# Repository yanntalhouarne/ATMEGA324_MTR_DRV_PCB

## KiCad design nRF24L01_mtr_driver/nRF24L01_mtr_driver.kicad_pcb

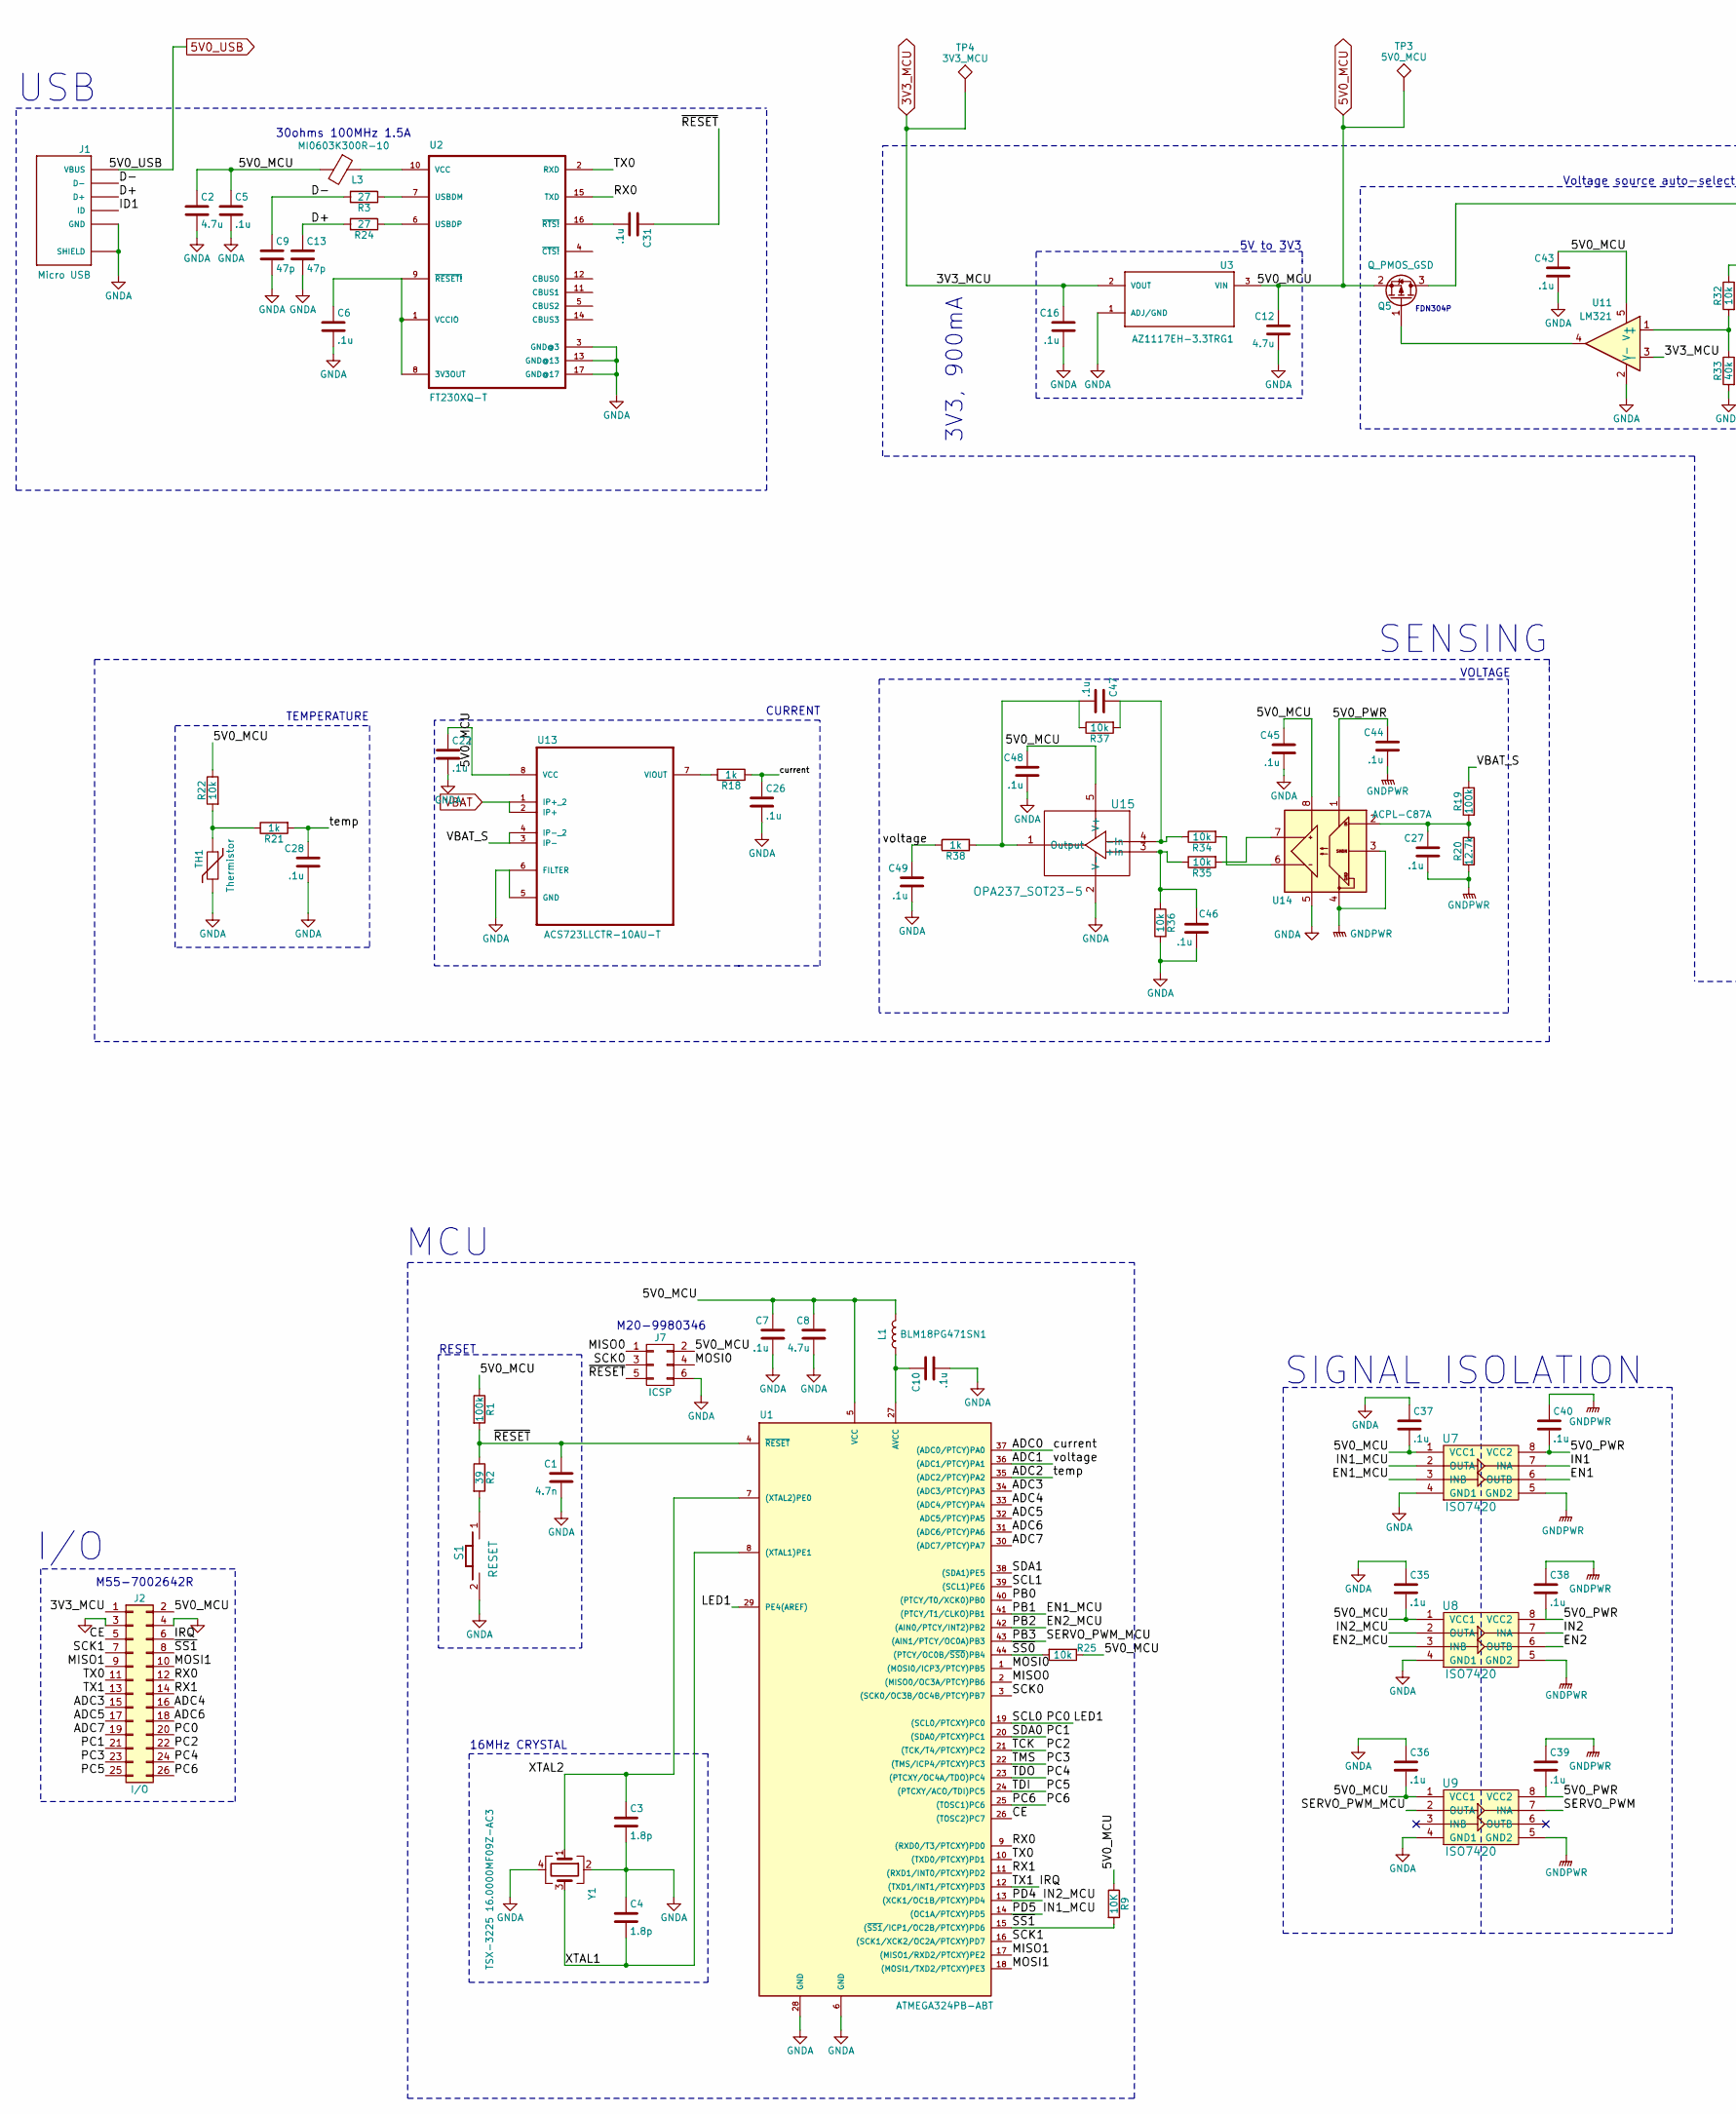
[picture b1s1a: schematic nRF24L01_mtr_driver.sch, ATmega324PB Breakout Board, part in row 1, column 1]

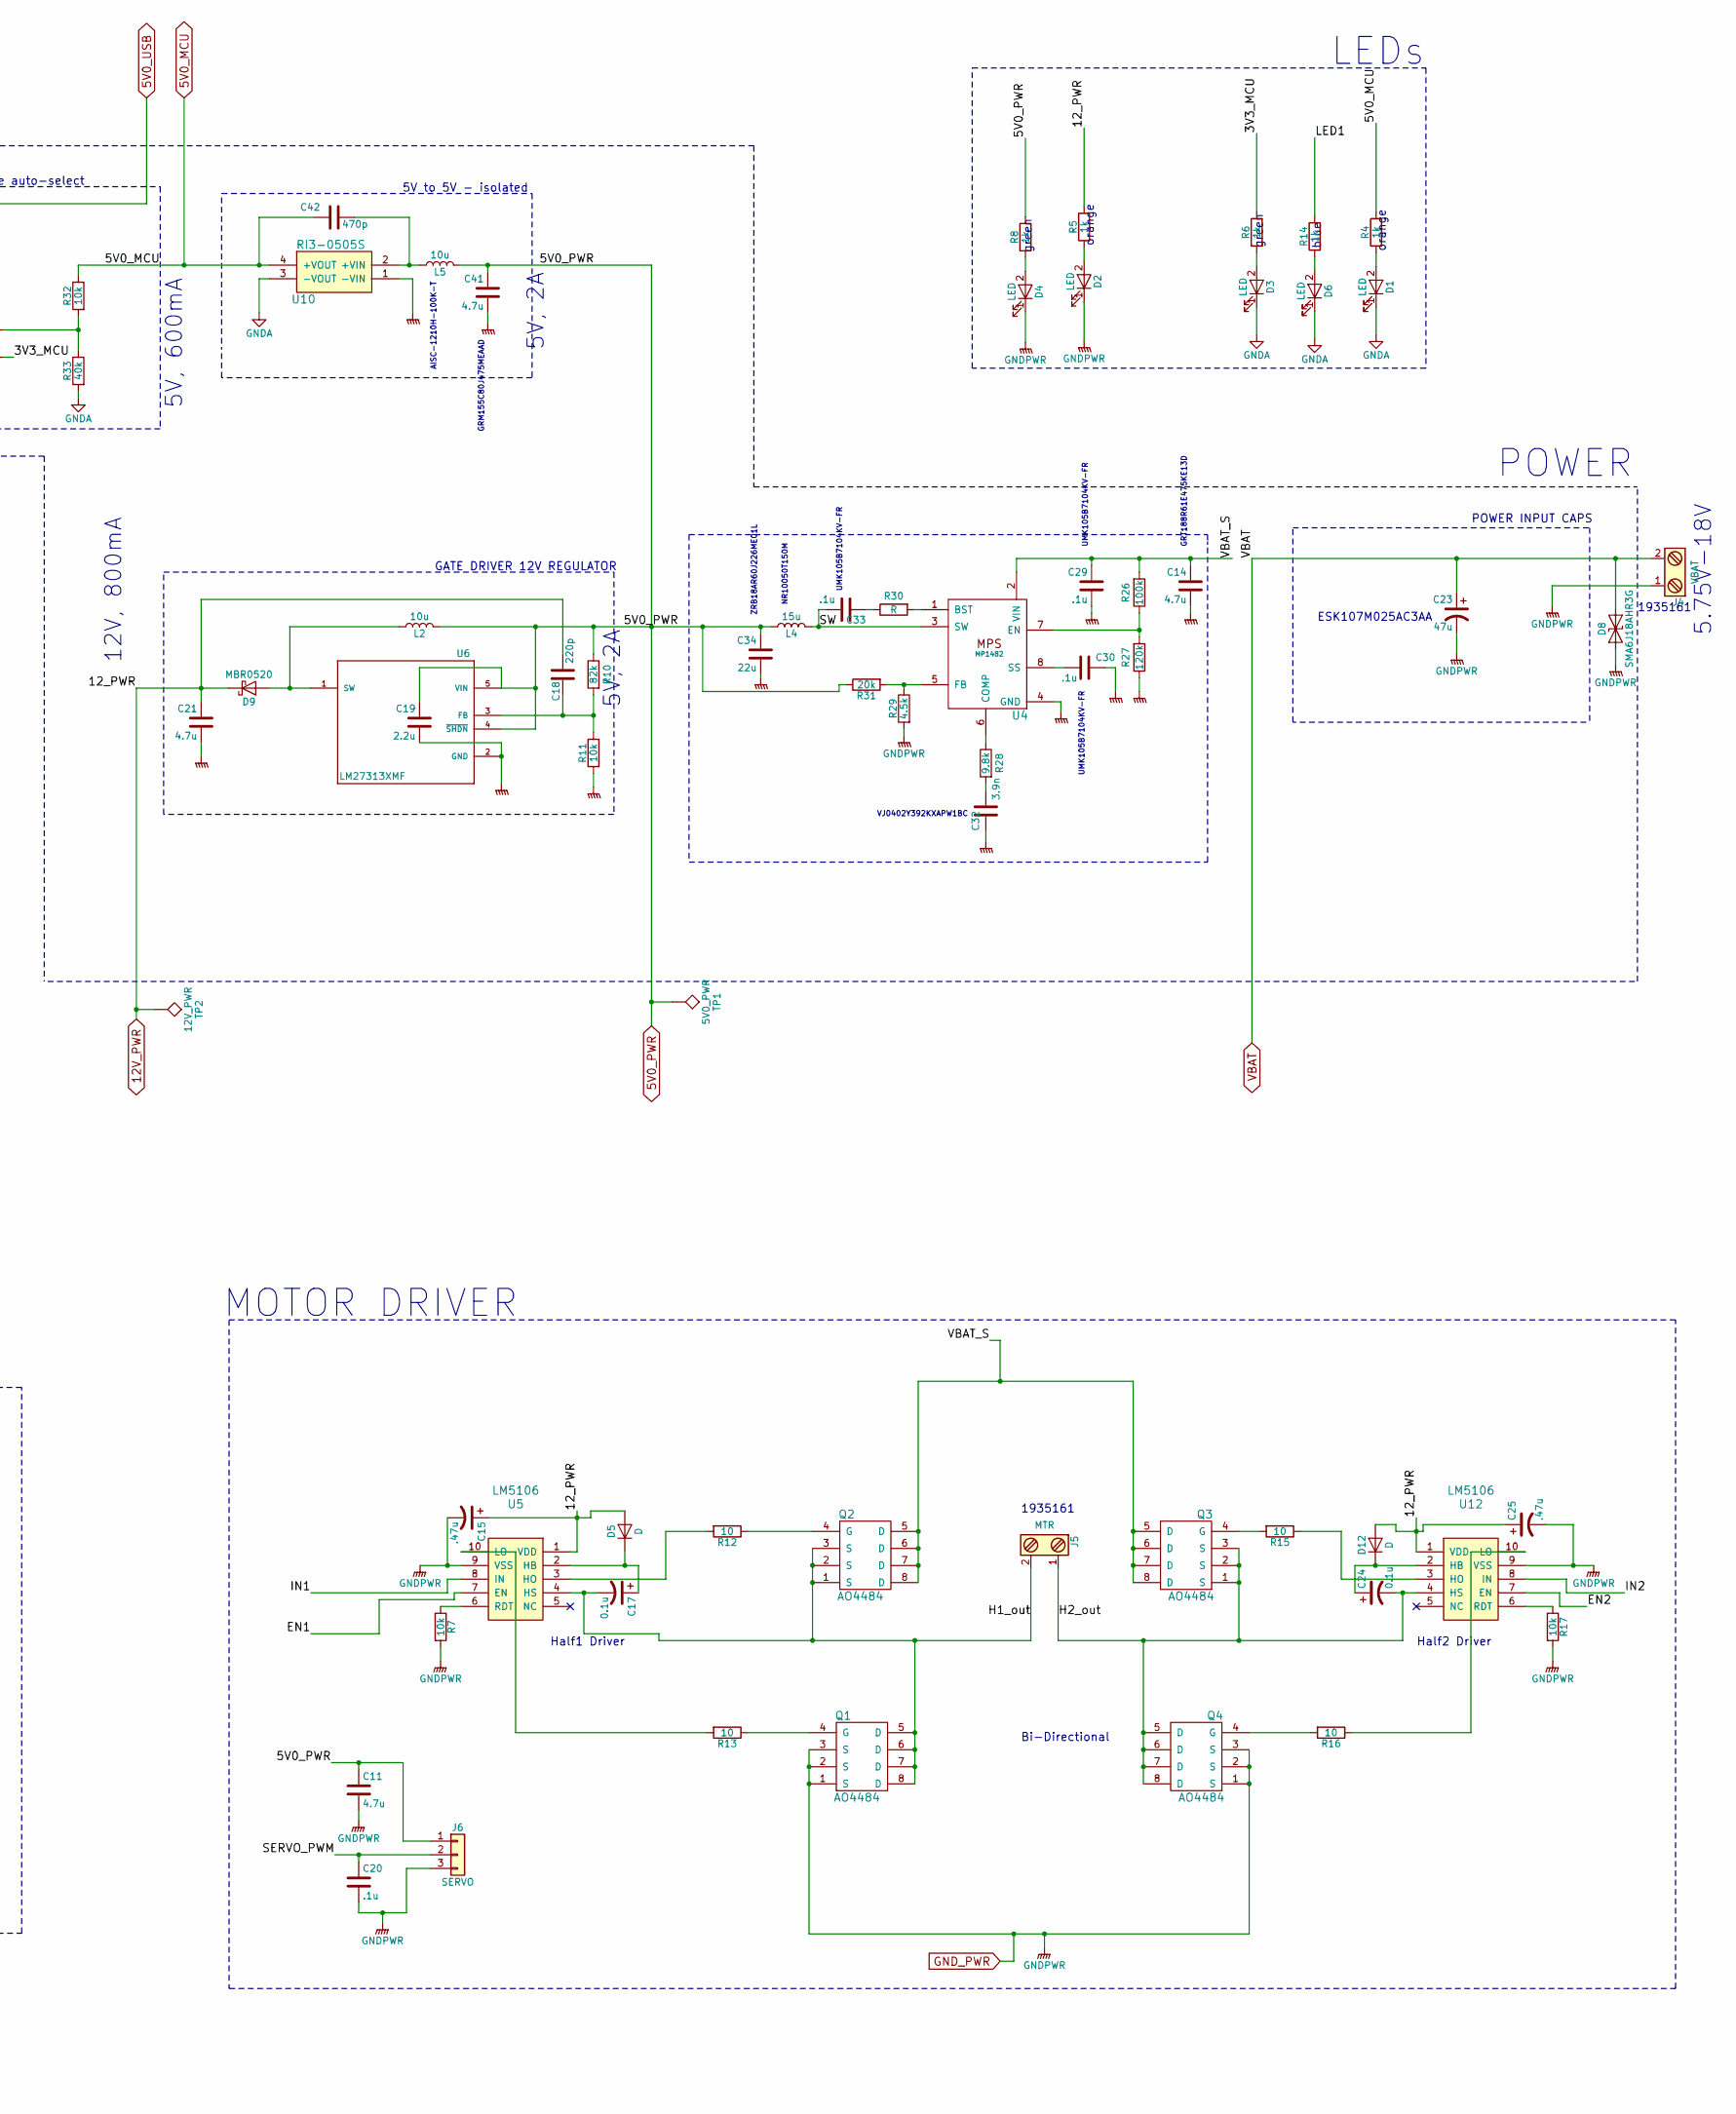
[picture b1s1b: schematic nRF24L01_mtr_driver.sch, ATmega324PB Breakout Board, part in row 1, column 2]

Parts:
C1: 4.7n; C_0402
C2, C11, C14: 4.7u; C_0603
C3, C4: 1.8p; C_0402
C5, C6, C7, C10, C16, C20, C22, C26, C27, C28, C30, C31, C33, C35, C36, C37, C38, C39, C40, C43, C44, C45, C46, C47, C48, C49: .1u; C_0402
C8, C12, C41: 4.7u; C_0402
C9, C13: 47p; C_0402
C15, C25: .47u; C_0603
C17, C24: 0.1u; C_0603
C18: 220p; C_0402
C19: 2.2u; C_0603
C21: 4.7u; C_0805
C23: 47u; D5_P2_cap
C29: .1u; C_0805
C32: 3.9n; C_0402
C34: 22u; C_0805
C42: 470p; C_0402
D1, D2, D3, D4, D6: LED; LED_0603
D5, D12: D; D_0603
D8: SMA6J18AHR3G; DO-214AC
D9: MBR0520; D_SOD-123
J1: Micro USB; USB_10118192-0001LF
J2: I/O; M55-60zzz42R
J4: VBAT; PHOENIX_1935161
J5: MTR; PHOENIX_1935161
J6: SERVO; Pin_Header_Straight_1x03_Pitch2.54mm
J7: ICSP; Pin_Header_Straight_2x03_Pitch2.54mm
L1: BLM18PG471SN1; L_0603
L2: 10u; C_0805
L3: MI0603K300R-10; L_0603
L4: 15u; SMD_1005
L5: 10u; L_1210
Q1, Q2, Q3, Q4: AO4484; SOIC-8-N
Q5: Q_PMOS_GSD; SOT-23
R1, R19, R26: 100k; R_0402
R2: 39; R_0402
R3, R24: 27; R_0402
R4, R5, R6, R8, R14, R18, R21, R38: 1k; R_0402
R7, R11, R17, R22, R25, R32, R34, R35, R36, R37: 10k; R_0402
R9: 10K; R_0402
R10: 82k; R_0402
R12, R13, R15, R16: 10; R_0402
R20: 12.7k; R_0402
R27: 120k; R_0402
R28: 9.8k; R_0402
R29: 4.5k; R_0402
R30: R; R_0402
R31: 20k; R_0402
R33: 40k; R_0402
S1: RESET; SW_SPST_KMR2
TH1: Thermistor; R_0603
TP1: 5V0_PWR; Measurement_Point_Square-SMD-Pad_Small
TP2: 12V_PWR; Measurement_Point_Square-SMD-Pad_Small
TP3: 5V0_MCU; Measurement_Point_Square-SMD-Pad_Small
TP4: 3V3_MCU; Measurement_Point_Square-SMD-Pad_Small
U1: ATMEGA324PB-ABT; QFP80P1200X1200X120-44N
U2: FT230XQ-T; QFN16
U3: AZ1117EH-3.3TRG1; SOT229P700X180-4N
U4: MP1482; ISO_7420
U5, U12: LM5106; VSSOP-8_2.4x2.1mm_Pitch0.5mm
U6: LM27313XMF; SOT95P285X120-5N
U7, U8, U9: ISO7420; ISO_7420
U10: RI3-0505S; ROE_0505S
U11: LM321; SOT-23-5
U13: ACS723LLCTR-10AU-T; SOIC-8-N
U14: ACPL-C87A; SSO-8_6.8x5.9mm_Pitch1.27mm_Clearance8mm
U15: OPA237_SOT23-5; SOT-23-5
Y1: TSX-3225 16.0000MF09Z-AC3

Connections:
3V3_MCU: C16.1, J2.1, R6.1, TP4.1, U3.2 (VOUT), U11.3 (-)
5V0_MCU: C2.1, C5.1, C7.1, C8.1, C12.1, C22.1, C35.2, C36.2, C37.2, C42.1, C43.1, C45.1, C48.1, J2.2, J7.2, L1.2, L3.2, Q5.2 (S), R1.1, R4.1, R9.1, R22.1, R25.1, R32.1, TP3.1, U1.5 (VCC), U3.3 (VIN), U7.1 (VCC1), U8.1 (VCC1), U9.1 (VCC1), U10.4 (+VOUT), U11.5 (V+), U13.8 (VCC), U14.8 (VDD2), U15.5 (V+)
5V0_PWR: C11.1, C19.1, C34.1, C38.2, C39.2, C40.2, C41.1, C44.1, J6.1, L2.1, L4.2, L5.1, R8.1, R10.1, R31.1, TP1.1, U6.4 (~SHDN), U6.5 (VIN), U7.8 (VCC2), U8.8 (VCC2), U9.8 (VCC2), U14.1 (VDD1)
5V0_USB: J1.1 (VBUS), Q5.3 (D)
12V_PWR: C15.1, C18.1, C21.1, C25.1, D5.2 (A), D9.1 (K), D12.2 (A), R5.1, TP2.1, U5.1 (VDD), U12.1 (VDD)
/ADC0: C26.1, R18.1, U1.37 ((ADC0/PTCY)PA0)
/ADC1: C49.1, R38.1, U1.36 ((ADC1/PTCY)PA1)
/ADC2: C28.1, R21.2, U1.35 ((ADC2/PTCY)PA2)
/ADC3: J2.15, U1.34 ((ADC3/PTCY)PA3)
/ADC4: J2.16, U1.33 ((ADC4/PTCY)PA4)
/ADC5: J2.17, U1.32 (ADC5/PTCY)PA5)
/ADC6: J2.18, U1.31 ((ADC6/PTCY)PA6)
/ADC7: J2.19, U1.30 ((ADC7/PTCY)PA7)
/CE: J2.5, U1.26 ((TOSC2)PC7)
/D+: C13.1, J1.3 (D+), R24.2
/D-: C9.1, J1.2 (D-), R3.2
/EN1: U5.7 (EN), U7.6 (OUTB)
/EN1_MCU: U1.41 ((PTCY/T1/CLKO)PB1), U7.3 (INB)
/EN2: U8.6 (OUTB), U12.7 (EN)
/EN2_MCU: U1.42 ((AIN0/PTCY/INT2)PB2), U8.3 (INB)
/H1_out: C17.2, J5.2, Q1.5 (D), Q1.6 (D), Q1.7 (D), Q1.8 (D), Q2.1 (S), Q2.2 (S), Q2.3 (S), U5.4 (HS)
/H2_out: C24.2, J5.1, Q3.1 (S), Q3.2 (S), Q3.3 (S), Q4.5 (D), Q4.6 (D), Q4.7 (D), Q4.8 (D), U12.4 (HS)
/ID1: J1.4 (ID)
/IN1: U5.8 (IN), U7.7 (INA)
/IN1_MCU: U1.14 ((OC1A/PTCXY)PD5), U7.2 (OUTA)
/IN2: U8.7 (INA), U12.8 (IN)
/IN2_MCU: U1.13 ((XCK1/OC1B/PTCXY)PD4), U8.2 (OUTA)
/IRQ: J2.6, J2.13, U1.12 ((TXD1/INT1/PTCXY)PD3)
/LED1: J2.20, R14.1, U1.19 ((SCL0/PTCXY)PC0), U1.29 (PE4(AREF))
/MISO0: J7.1, U1.2 ((MISO0/OC3A/PTCY)PB6)
/MISO1: J2.9, U1.17 ((MISO1/RXD2/PTCXY)PE2)
/MOSI0: J7.4, U1.1 ((MOSI0/ICP3/PTCY)PB5)
/MOSI1: J2.10, U1.18 ((MOSI1/TXD2/PTCXY)PE3)
/PB0: U1.40 ((PTCY/T0/XCK0)PB0)
/PB3: U1.43 ((AIN1/PTCY/OC0A)PB3), U9.2 (OUTA)
/PC1: J2.21, U1.20 ((SDA0/PTCXY)PC1)
/PC2: J2.22, U1.21 ((TCK/T4/PTCXY)PC2)
/PC3: J2.23, U1.22 ((TMS/ICP4/PTCXY)PC3)
/PC4: J2.24, U1.23 ((PTCXY/OC4A/TDO)PC4)
/PC5: J2.25, U1.24 ((PTCXY/ACO/TDI)PC5)
/PC6: J2.26, U1.25 ((TOSC1)PC6)
/RX0: J2.12, U1.9 ((RXD0/T3/PTCXY)PD0), U2.15 (TXD)
/RX1: J2.14, U1.11 ((RXD1/INT0/PTCXY)PD2)
/SCK0: J7.3, U1.3 ((SCK0/OC3B/OC4B/PTCY)PB7)
/SCK1: J2.7, U1.16 ((SCK1/XCK2/OC2A/PTCXY)PD7)
/SCL1: U1.39 ((SCL1)PE6)
/SDA1: U1.38 ((SDA1)PE5)
/SERVO_PWM: C20.1, J6.2, U9.7 (INA)
/SW: C33.1, L4.1, U4.3 (SW)
/TX0: J2.11, U1.10 ((TXD0/PTCXY)PD1), U2.2 (RXD)
/VBAT_S: C14.1, C29.1, Q2.5 (D), Q2.6 (D), Q2.7 (D), Q2.8 (D), Q3.5 (D), Q3.6 (D), Q3.7 (D), Q3.8 (D), R19.1, R26.2, U4.2 (VIN), U13.3 (IP-), U13.4 (IP-_2)
/XTAL1: C4.2, U1.8 ((XTAL1)PE1), Y1.3
/XTAL2: C3.1, U1.7 ((XTAL2)PE0), Y1.1
/~RESET: C1.1, C31.1, J7.5, R1.2, R2.1, U1.4 (~RESET)
/~SS0~: R25.2, U1.44 ((PTCY/OC0B/~SS0~)PB4)
/~SS1~: J2.8, R9.2, U1.15 ((~SS1~/ICP1/OC2B/PTCXY)PD6)
GNDA: C1.2, C2.2, C3.2, C4.1, C5.2, C6.2, C7.2, C8.2, C9.2, C10.2, C12.2, C13.2, C16.2, C22.2, C26.2, C28.2, C35.1, C36.1, C37.1, C43.2, C45.2, C46.2, C48.2, C49.2, D1.1 (K), D3.1 (K), D6.1 (K), J1.5 (GND), J1.6 (SHIELD), J1.7 (SHIELD), J1.8 (SHIELD), J1.9 (SHIELD), J2.3, J2.4, J7.6, R33.2, R36.1, S1.2, TH1.2, U1.6 (GND), U1.28 (GND), U2.3 (GND@3), U2.13 (GND@13), U2.17 (GND@17), U3.1 (ADJ/GND), U7.4 (GND1), U8.4 (GND1), U9.4 (GND1), U10.3 (-VOUT), U11.2 (V-), U13.5 (GND), U13.6 (FILTER), U14.5 (GND2), U15.2 (V-), Y1.2, Y1.4
GND_PWR: C11.2, C14.2, C15.2, C19.2, C20.2, C21.2, C23.2, C25.2, C27.2, C29.2, C30.1, C32.2, C34.2, C38.1, C39.1, C40.1, C41.2, C44.2, D2.1 (K), D4.1 (K), D8.2 (A2), J4.1, J6.3, Q1.1 (S), Q1.2 (S), Q1.3 (S), Q4.1 (S), Q4.2 (S), Q4.3 (S), R7.2, R11.2, R17.2, R20.2, R27.1, R29.2, U4.4 (GND), U5.9 (VSS), U6.2 (GND), U7.5 (GND2), U8.5 (GND2), U9.5 (GND2), U10.1 (-VIN), U12.9 (VSS), U14.3 (IN-), U14.4 (GND1)
unnamed: C6.1, U2.1 (VCCIO), U2.8 (3V3OUT), U2.9 (~RESET!~)
unnamed: C10.1, L1.1, U1.27 (AVCC)
unnamed: C17.1, D5.1 (K), U5.2 (HB)
unnamed: C18.2, R10.2, R11.1, U6.3 (FB)
unnamed: C24.1, D12.1 (K), U12.2 (HB)
unnamed: C27.1, R19.2, R20.1, U14.2 (IN)
unnamed: C30.2, U4.8 (SS)
unnamed: C31.2, U2.16 (~RTS!~)
unnamed: C32.1, R28.2
unnamed: C33.2, R30.1
unnamed: C42.2, L5.2, U10.2 (+VIN)
unnamed: C46.1, R35.1, R36.2, U15.3 (+In)
unnamed: C47.1, R34.1, R37.2, U15.4 (-In)
unnamed: C47.2, R37.1, R38.2, U15.1 (Output)
unnamed: D1.2 (A), R4.2
unnamed: D2.2 (A), R5.2
unnamed: D3.2 (A), R6.2
unnamed: D4.2 (A), R8.2
unnamed: D6.2 (A), R14.2
unnamed: D9.2 (A), L2.2, U6.1 (SW)
unnamed: L3.1, U2.10 (VCC)
unnamed: Q1.4 (G), R13.1
unnamed: Q2.4 (G), R12.1
unnamed: Q3.4 (G), R15.2
unnamed: Q4.4 (G), R16.2
unnamed: Q5.1 (G), U11.4
unnamed: R2.2, S1.1
unnamed: R3.1, U2.7 (USBDM)
unnamed: R7.1, U5.6 (RDT)
unnamed: R12.2, U5.3 (HO)
unnamed: R13.2, U5.10 (LO)
unnamed: R15.1, U12.3 (HO)
unnamed: R16.1, U12.10 (LO)
unnamed: R17.1, U12.6 (RDT)
unnamed: R18.2, U13.7 (VIOUT)
unnamed: R21.1, R22.2, TH1.1
unnamed: R24.1, U2.6 (USBDP)
unnamed: R26.1, R27.2, U4.7 (EN)
unnamed: R28.1, U4.6 (COMP)
unnamed: R29.1, R31.2, U4.5 (FB)
unnamed: R30.2, U4.1 (BST)
unnamed: R32.2, R33.1, U11.1 (+)
unnamed: R34.2, U14.6 (OUT-)
unnamed: R35.2, U14.7 (OUT+)
VBAT: C23.1, D8.1 (A1), J4.2, U13.1 (IP+_2), U13.2 (IP+)

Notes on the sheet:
Half1 Driver
Half2 Driver
Bi-Directional
POWER INPUT CAPS
GATE DRIVER 12V REGULATOR
RESET
16MHz CRYSTAL
USB
LEDs
POWER
MCU
MOTOR DRIVER
SENSING
CURRENT
VOLTAGE
TEMPERATURE
1935161
ESK107M025AC3AA
orange
green
blue
5.75V-18V
5V, 2A
12V, 800mA
5V to 5V - isolated
5V to 3V3
SIGNAL ISOLATION
Voltage source auto-select
30ohms 100MHz 1.5A
GRT188R61E475KE13D
UMK105B7104KV-FR
VJ0402Y392KXAPW1BC
NR10050T150M
ZRB18AR60J226ME01L
GRM155C80J475MEAAD
AISC-1210H-100K-T
FDN304P
M55-7002642R
I/O
5V, 600mA

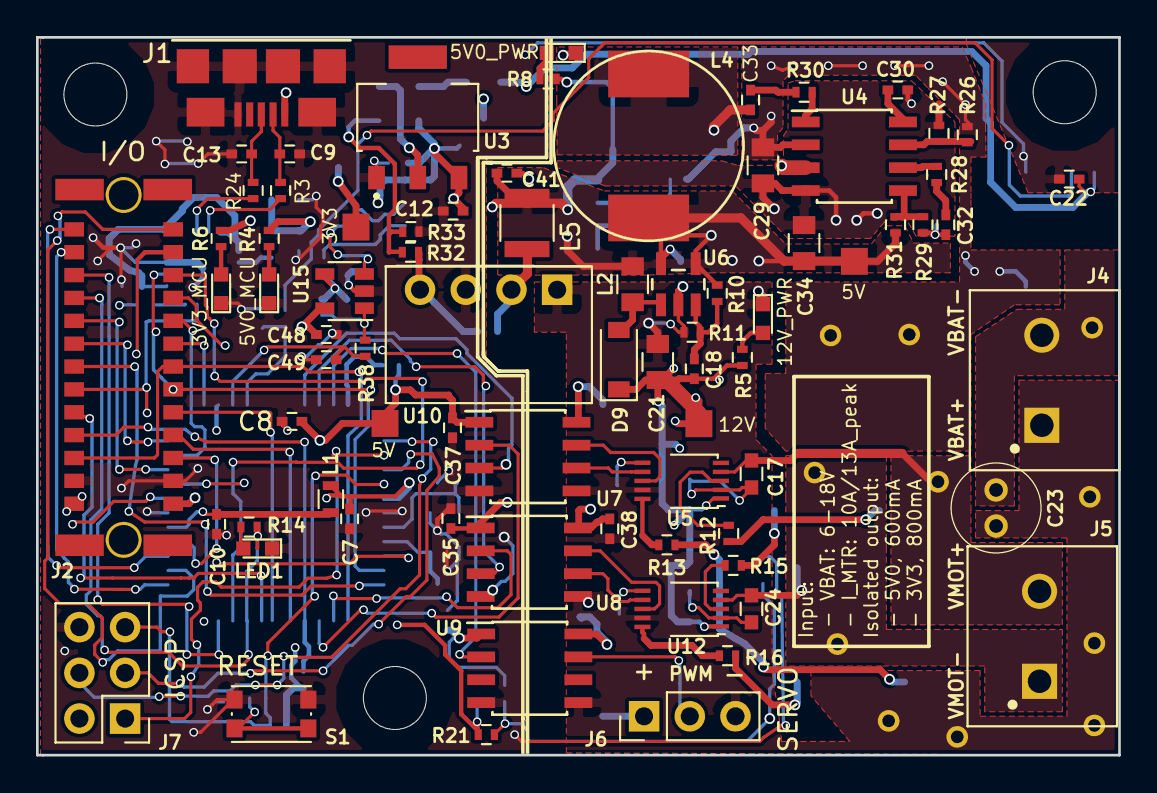
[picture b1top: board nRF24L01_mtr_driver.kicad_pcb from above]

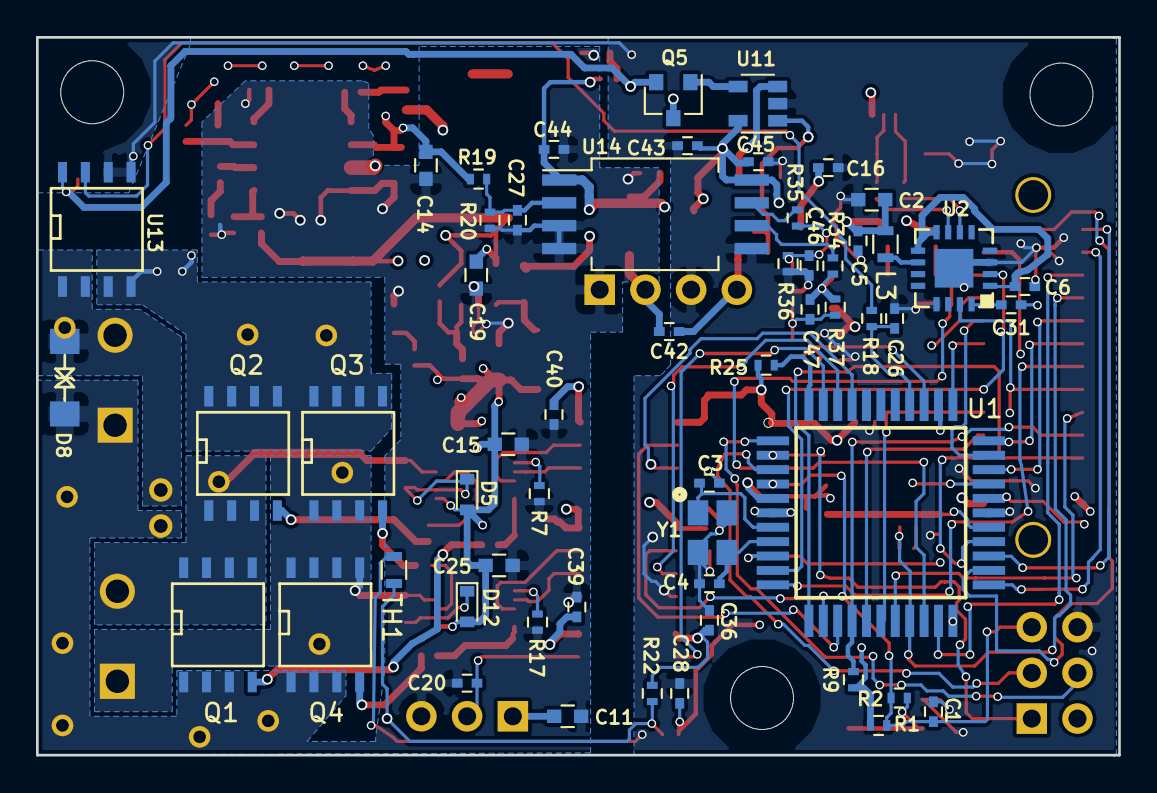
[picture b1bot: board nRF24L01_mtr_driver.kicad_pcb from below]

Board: 4 copper layers, 60.1 x 39.9 mm, 133 parts (56 on the bottom side), 99 nets.

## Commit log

2019-02-23 Added schematic, still need to isolate voltage sense signal
2019-02-24 added voltage sense isolation, needs routing
2019-02-24 Changed the footprint of some 0603 cpacitors to 0402 to save space
2019-02-24 placed major coponents, no routing
2019-02-25 placed most components
2019-02-25 23 components left, stil needs routing
2019-02-28 arranged silkscreen, started rounting (ftdi)
2019-03-16 ready for 2 or 4 layer implementation
2019-03-17 logic side rounting done (4 layer)
2019-03-17 added LED1
2019-03-17 4-layer, most of the routing done (logic + pwr)
2019-03-18 copper pour plane zones done
2019-03-24 All pour planes finalized
2019-03-24 fixed VABT and GND_PWR planes for C23, 43 unconnections left
2019-03-24 7 unconnections let
2019-03-24 finsihed routing, added 3D model for IO connector, still needs silckcreen touchup
2019-03-24 silkscreen touch-up done, added AMS117 and Block Term 3D models
2019-03-25 fixed ROI-0505S footprint and added its 3 model
2019-03-29 fixed U14 position
2019-03-31 generated new gerber files
2019-04-07 Added BOM, changed Vin_min to 6V on silkscreen
2019-04-07 added step files for two-pcb stak up
2019-04-11 updated BOM for missing components
